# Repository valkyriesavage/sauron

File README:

Sauron
======
Sauron is a tool for prototyping functional objects, like video game
controllers, DJ mixers, or ergonomic mice. It works on computer vision, so
you don't have to spend time wiring up each button or joystick that you want
in your final prototype: a single camera can see them all.

The way it works is this: first, you create a 3D model of your object in
Solidworks, and put in special tagged geometry so Sauron knows what to look
for:

Then, you add in a 3D model which represents the camera you plan to use for
sensing. It's field of vision also needs to be modeled and tagged:

As you start working through the user interface, Sauron will do some analysis
on the locations of the parts in your object:

First, we decide if there's anything that already falls in the camera's
field of view (FOV). In this case, the joystick and D-Pad on the front
of the controller are already visible.

So we ignore those.

Sauron can also extrude pieces to go into the camera's field of view. The
bumper buttons on the side of the controller were processed in this way:

Originally they were stumpy little tagged geometry pieces,

But we just stretch them until they reach the FOV cone.

So, those are done once we extend them.

So we'll ignore them for now.

These buttons in the back are a different problem. We could extend them until
they hit the FOV cone, but unfortunately they'll hit the controller body if we
do that. Sauron does simulation to check, and finds that that's true.

So we'll have to go for plan B. Sauron's plan B is mirrors. We can figure out
where the mirrors need to go by doing raycasting: the camera sends out a bunch
of rays, looks at where they go after they bounce off the inside surface of the
controller, and checks to see if any of them actually hit the buttons we're
looking for. All the ones that do are shown here. Sauron will put stars to
indicate where a mirror should go after printing (the camera will be able
to see the reflection of the buttons in the mirror):

So, all put together, our processed controller looks like this:

And when we print it out, we attach the camera that we modeled, color the
buttons, add the mirrors, and show it to the computer vision algorithms.
Then we're set to go!

Sauron supports several kinds of inputs, which have different kinds of
motion, like buttons, dials, trackballs, and sliders.
![modeled object](images/sauron-inputs.png "Sauron takes a wide range
of inputs!") 
You can make your own inputs if you want to code up the computer vision
algorithms for them, but you can also just modify the existing inputs
to fit your needs, like turning a dial into a volume knob or a DJ
mixing wheel:

The computer vision works in different ways depending on the way the
component moves. You can dig around and check it out, but the gist
is this:

Technical Details
=================
The Sauron model-modification tool is written as a plugin for SolidWorks.
I wrote and tested it on SW2012, but theoretically it will work in newer
versions of that tool. The computer vision subsystems are written with
OpenFrameworks, and everything in here communicates via OSC messages.

Here there be Dragons
=====================
This code was written as a part of my PhD, and thus it can be sketchy in
some places! It's not very well documented, but I wanted to provide it
on github for anyone curious about spelunking through it and hopefully
making use of it in some way.

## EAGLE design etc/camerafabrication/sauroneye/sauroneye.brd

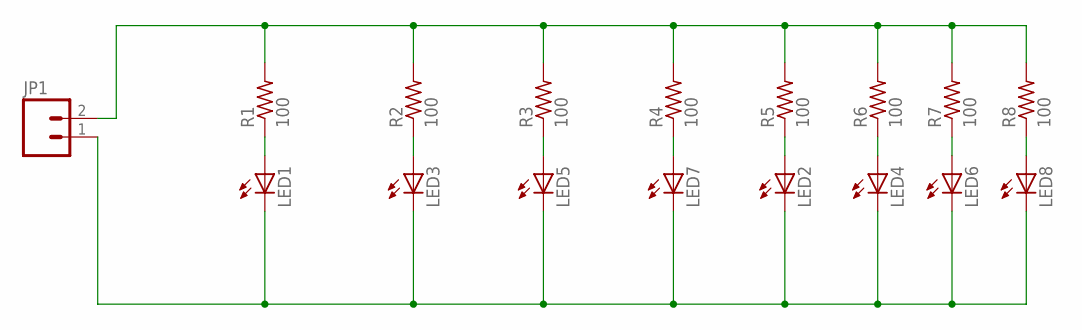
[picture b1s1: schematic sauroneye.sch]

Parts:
JP1: M02PTH; 1X02
LED1, LED2, LED3, LED4, LED5, LED6, LED7, LED8: LEDCHIP-LED0805; CHIP-LED0805
R1, R2, R3, R4, R5, R6, R7, R8: 100; R0805

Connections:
unnamed: JP1.2, R1.2, R2.2, R3.2, R4.2, R5.2, R6.2, R7.2, R8.2
unnamed: LED1.A, R1.1
unnamed: LED3.A, R2.1
unnamed: LED5.A, R3.1
unnamed: LED7.A, R4.1
unnamed: JP1.1, LED1.C, LED2.C, LED3.C, LED4.C, LED5.C, LED6.C, LED7.C, LED8.C
unnamed: LED2.A, R5.1
unnamed: LED4.A, R6.1
unnamed: LED6.A, R7.1
unnamed: LED8.A, R8.1

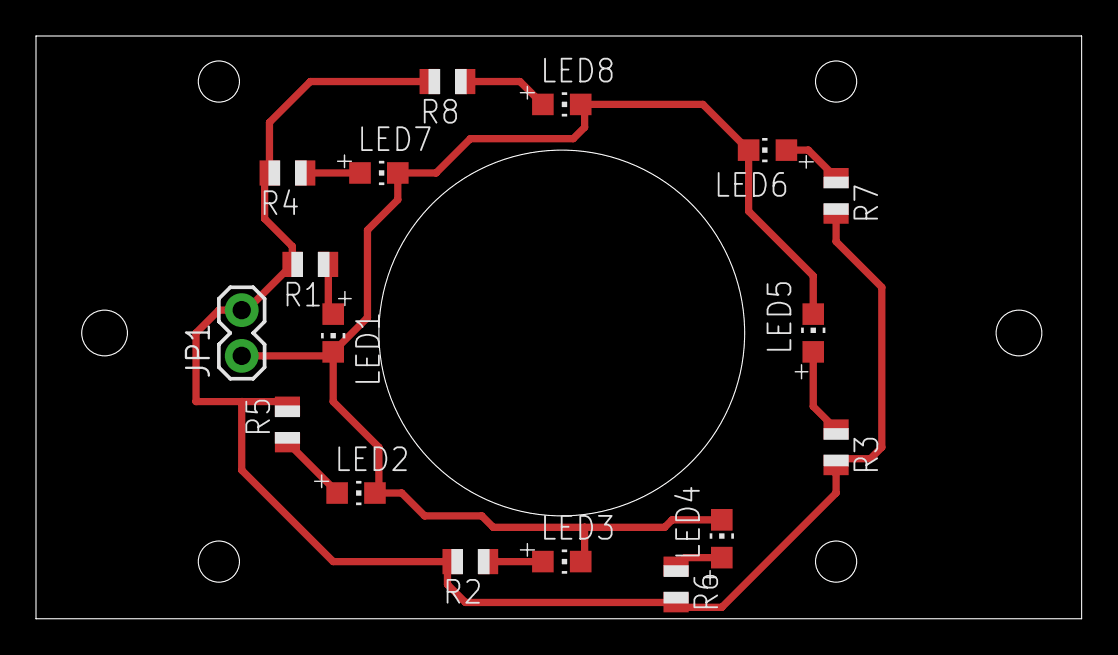
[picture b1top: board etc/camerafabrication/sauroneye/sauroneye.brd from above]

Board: 2 copper layers, 58.1 x 32.4 mm, 17 parts (0 on the bottom side), 10 nets.

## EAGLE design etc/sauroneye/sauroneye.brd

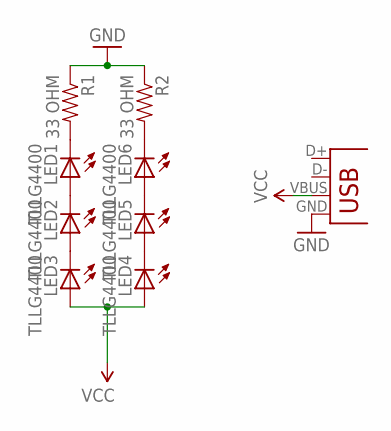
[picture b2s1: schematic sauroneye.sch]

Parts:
LED1, LED2, LED3, LED4, LED5, LED6: TLLG4400; LED3MM
R1, R2: 33 OHM; AXIAL-0.3
X1: USBSMD; USB-MINIB

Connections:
GND: R1.P$1 (1), R2.P$1 (1), X1.GND
unnamed: LED6.K (C), R2.P$2 (2)
unnamed: LED1.K (C), R1.P$2 (2)
unnamed: LED5.K (C), LED6.A
unnamed: LED4.K (C), LED5.A
unnamed: LED1.A, LED2.K (C)
unnamed: LED2.A, LED3.K (C)
VCC: LED3.A, LED4.A, X1.VBUS

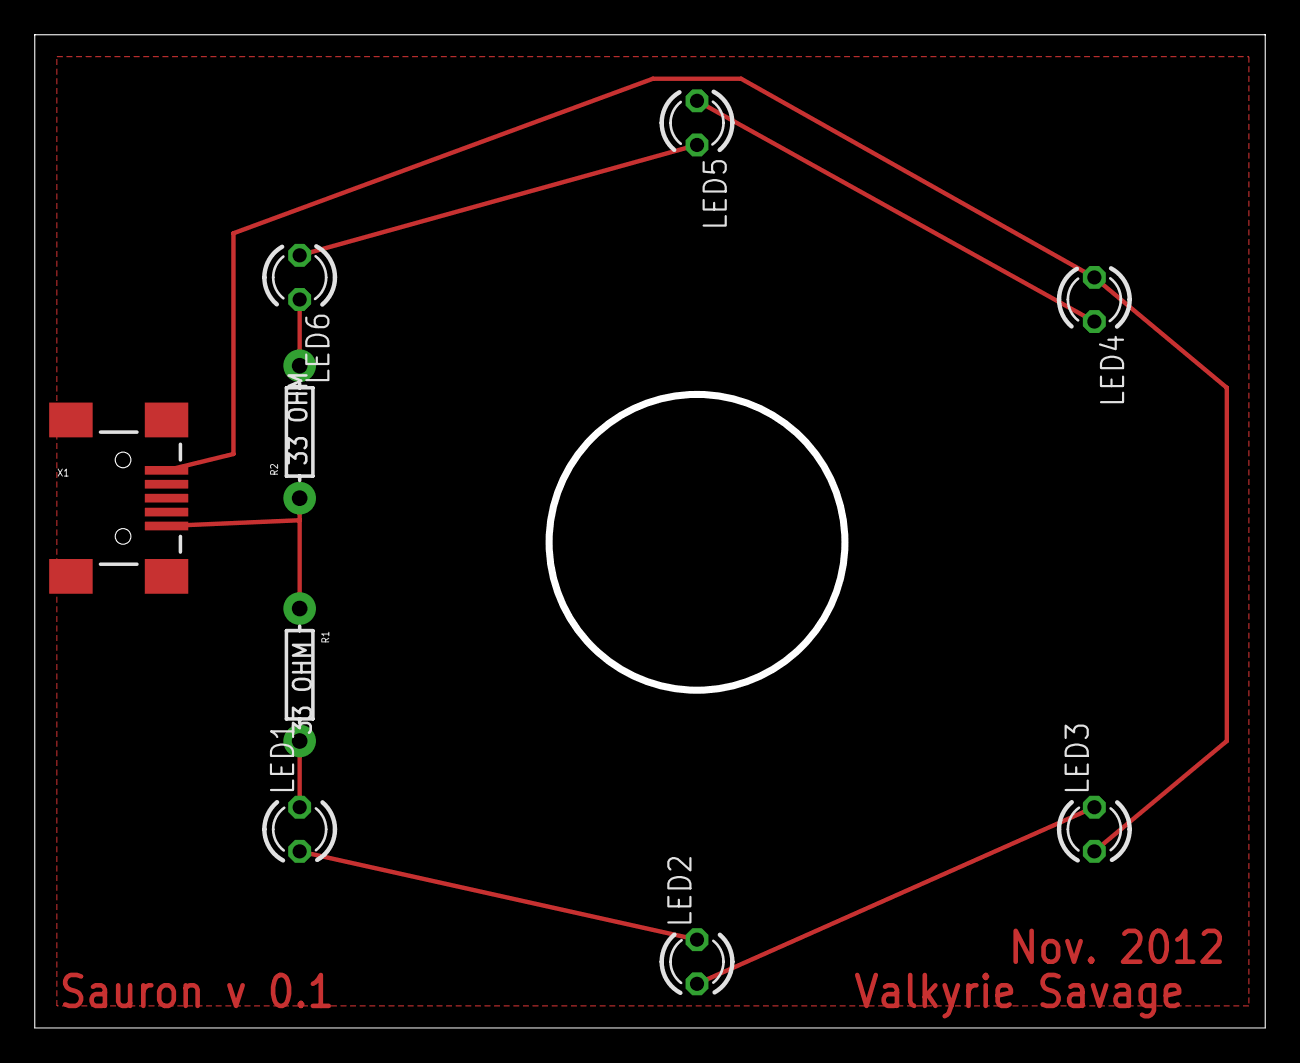
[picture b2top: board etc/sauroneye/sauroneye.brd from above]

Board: 2 copper layers, 70.4 x 56.7 mm, 9 parts (0 on the bottom side), 8 nets.

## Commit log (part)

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2012-07-09 Initial commit with skeleton README abstract
2012-07-11 small iterations on mockup
2012-08-09 adding gitignore
2012-08-10 BinaryRings update
    * ridges are now wider
    * colors for better visibility
    * measurement arm for wires, includes guides and a skirt to keep its
    place
2012-08-11 Switch.scad
    * it seems useful to have a switch description that we can just
    subtract out or add in to a model
2012-08-23 Switch ring and update to switch
    * switch ring like the one in the animal sounds toy
    * switch is now properly a module
2012-11-04 First version of vision algorithm, totally crippled
    * The vision algorithm is now something that I found online
    which displays interesting corners to track
    * Thanks to kristi.tsukida@gmail.com for putting it out there!
2012-11-05 Return a list of threshold-exceeding points
    * can do more calculation on them!
2012-11-09 circuit board for around eye camera
    * has a cutout for the eye to fit through
    * has 6 IR LEDs around to light the space
2012-11-12 update to board
    * board now obeys physics and laws of electricity
    * board has USB connector
    * removing whatever those spurious eagle files are and ignoring them
    in the future
2012-11-14 SolidWorks design for first interactive object
    * button - need to iterate on this; currently only vertical motion
    and we need horizontal
    * dial
    * slider
    * dpad - will need physical testing for springs
    * body - should hold point grey camera + extra IR LED board
2012-11-15 Calibration page for Point Grey Camera
    * a page with one inch squares on it so we can
    determine FOV and lens angle for the point grey
2012-11-20 modify for printing and camera measurements
    * now should be printable, the box1
    * now takes into account PS3 EYE FOV
    * started on slider+joystick box
    * slider and joystick both modeled
2012-11-21 joystick ready to print, i think
    * modified part to fit together!
    * joystick obeys physics!
    * yayyyyyyyy
    * let's print it
2012-11-26 paper skeleton
    * woooooooooo paper!
2012-11-30 skeleton for component trackers
    * need to implement all detection algorithms
    * need to figure out if contourfinder finds blobs in the same
    order each time
    * need to test!
2012-12-05 everything should compile now, fixed some compiler errors and re-indented header file
2012-12-12 change board opening to hold ps3 eye, change to work properly with smc usb connector
2012-12-12 sauroneye board bugfixing
2012-12-12 paper starting!
    * paper formatted correctly
    * sauron example image
    * now to write a bunch...
2012-12-13 more paper fleshing-out
2012-12-16 paper work
2012-12-16 related work
2012-12-19 photos of hardware setup
2012-12-27 added a testing thing which still needs work, working on redoing some of the coding for tracking
2013-01-09 bjoern's comments
2013-01-11 moved from CHI-WIP to UIST to reflect real life..
2013-01-14 moving to UIST folder from CHI folder
    * remove extraneous CHI class
    * having issues with TeX; it won't take all the files
    at once...
2013-01-14 start on controller-shaped thing
    * git ignore solidworks "file open" files
    * dpad post size changes
    * minor modifications to box
    * 4-post style button for even springiness
    * xbox-style body with button holes and dpad holes so far (need
    joystick)
2013-01-17 iteration
2013-01-22 moved some stuff, finished some models!
    * moved a few of the button assemblies into their own folders
    to avoid clutter
    * finished the multi-linkage button of Bjoern's design
    * finished adding the joystick to the XBOX-style controller
    * finished a preliminary design for a button with a whippy thing
    which could be better than the multi-linkage solution?
2013-01-27 resolved 'ISO forbids initialization of member' error. see: -http://www.cplusplus.com/forum/beginner/37023/ -http://stackoverflow.com/questions/177437/const-static
2013-02-01 finally figure out how to work with SW API in VS, about to upgrade to using VS2012 Professional, so this is a checkpoint
2013-02-02 registration: added more structure and some bulk
2013-02-04 outline of how to capture slider bounds
2013-02-05 experimenting with configurations, fixed FOV objects to be more accurate, playing around with features
2013-02-06 added a cin utility function
2013-02-08 modifications for ease of coding
2013-02-09 utilities: added bounding box utility function
2013-02-10 should now be able to read the percentage progress of a slider in a horizontal environemnt. Testing with a printed controller pending. Limited functionality to ensure I'm doing it correctly (so, pend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
2013-02-13 refactored slider stuff and started with dial detection/calculation
2013-02-17 more dial work -some utility methods (distanceFormula, midpoint) -redid dial registration methods to reflect actuality of how blobs will appear to camera -progress detection, feedback pending
2013-02-18 configurations now work
    * can create and activate configurations of parts instead of using the
    copy-a-part method.
    * yay!
2013-02-18 now generate configurations, can't get it to do extrusion correctly
    * still working on extrusion
    * about to start experiments with measurement... maybe we can
    just extrude that way for now.
2013-02-18 modifications to make coding easier
2013-02-21 frustratingly, extrusion depth change still does not work properly. we can change in default config only, and only when we are in another config. then we cannot automatically change back and have the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
2013-02-22 scroll wheel progress
    -todo: have it not show 'none' direction unconditionally
2013-02-23 cleaned up, refactored, and added message sending message will send to 'componenttype/id/componentmeasurement'
2013-02-24 cleaned up a bit
2013-02-25 prepared registration for receiving messages from SW. Pressing 'r' simulates receving a start message and starting registration, pressing 'd' simulates receiving a finish message and stopping registr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
2013-02-26 now movement sensitive recognition is available for slider, dial, button and scroll_wheel
2013-02-27 looking at measure vs closest distance and feature vs config
    * still having default issues
    * still can't get accurate distance measurements
2013-02-27 AUTOMATICALLY MODIFIED MODELS!
    * many of these changes were automatic! by the plugin!
    * other changes are related to reorganizing the folder so i don't
    go insane
2013-03-01 added a bit of graphical niceties -informing the user what component is being registered
2013-03-01 cleaned up component registration
2013-03-02 added joystick support. -coordinate output isn't that meaningful to the region of interest yet. But it does offer correlative information to the position of the joystick
2013-03-02 removed old unused code
2013-03-03 messed around with movement threshold (still haven't settled on a good one), also corrected window size.
2013-03-05 altered joystick measurement so now points are relative to joystick's region of interest
2013-03-06 interface mockups for bjoern class
2013-03-06 some modifications...
2013-03-07 function signature and component size
    * changed function signature from bool to correct void
    * upped minimum trackable component size to 15 from 5 in order to
    reduce noise
2013-03-07 nasty node-ness
    * not sure if all this stuff has to be in the working directory, but
    here it is!
    * this is the addition of the node.js modules required to repeat the
    osc messages from the CV code over to WebSockets
    * note that to run this, one needs to install node
2013-03-07 add an ack for mark
2013-03-08 cleaned up ComponenTracker construction. -mThreshold at 2.0f seems like a good guess
2013-03-08 Dial measurements now make sense according to a 360 degree circle of completion. Return is in degrees -ok you'll probably want to choose between degrees and radians so I added that in
2013-03-08 improved scroll wheel feedback. Still has some quirks like sometimes it fails to pick up direction
2013-03-08 trying to get raytracing to work... slightly works now in that it no longer crashes solidworks
2013-03-08 enforce ordering of button pushes, export STL file after removing camera, then replace camera
2013-03-10 0th order ray-tracing works!
    * thanks be to Artem Taturevych of Intercad for all his help in
    the SolidWorks forums. progress!
    * this simplified version of raytracing only casts one ray from
    the origin in the z direction and checks to see if it hits the
    selected solid body, then visualizes the points where it does
2013-03-10 make button have just one solid body
2013-03-10 images for the generated web instructions
2013-03-10 added camera holders to the two hand-tuned components (need to tweak for actual camera measurements), slid stuff around
2013-03-10 hand-tuned button with mirror setup to show how to place mirrors to alter button direction
2013-03-11 update camera model
    * real measurements!
    * change many models to reflect the actual size!
2013-03-12 remodeled things to have correct taps for camera mounting, dodecahedron, mirror thing, and linkage button are all ready to print
2013-03-12 fresh solidworks mockup with just one interface
2013-03-12 small paper tweak
2013-03-13 still raytracing...
2013-03-13 try out the joystick as a dpad, thicken the dpad thingies
2013-03-15 changes mostly to related work
2013-03-18 extrusion now works really really well
    * updated measurement between a part and the FOV to cast a ray in the
    direction of the flag protrusion... this gives the best reading and
    can also reliably tell when we won't be able to reach the FOV
    * updated all components to have the correct features to make this ray
    casting work properly
2013-03-18 some figures
2013-03-18 some bits about assembly mate moving (does not work) and some bits about checking to see if other components block rays
2013-03-20 added example images into instructions
    * generated instructions now show images
    * yay!
2013-03-20 put joystick part to replace assembly in controller
2013-03-21 tweaked some figures, added comments
2013-03-23 joystick readjusted so middle is (0,0) and fixed a joystick bug (the bug was trying to make calculations across every blob in the view (including those outside it's ROI) which obviously won't work).
2013-03-25 paper work, new figures
2013-03-25 ergonomic mouse first cut
2013-03-25 abstractions are nice
2013-03-25 added some ComponentTracker documentation
2013-03-26 updated and new figures, language, bits of evaluation, hooray
2013-03-26 edge cases
2013-03-26 added some documentation
2013-03-27 added some arduino test code (untested)
2013-03-27 multinub button for figure now working
2013-03-27 sad and broken
2013-03-28 just add in the else to keep away from that weird case where they are both set
2013-03-28 remove TODO
2013-03-28 extrusion failure figure
2013-03-29 quick check will highlight which components are visible or not to the camera
2013-03-29 new figures from xbox processing and more, with one figure ugly and incomplete (the arch one)
2013-03-30 add a flag for black vs white prints, revert dial to previous sensing
2013-03-31 Bjoern's pass over related work
2013-04-02 extra sentence in limitations
2013-04-02 updated figures, some work on wording
2013-04-02 updated dpad algorithm to something more reasonable
2013-04-02 figures and video clips
2013-04-02 figures that i thought went away
2013-04-02 last of sw images, i do believe
2013-04-04 pass over pages 1-3
2013-04-04 game now accepts osc messages, should process them correctly
2013-04-04 this demo code now works
2013-04-04 i thought this was already gone?
2013-04-04 comment resolution
2013-04-05 typos and a new figureeeee
2013-04-05 fixed figure to have reference letters
2013-04-05 notes about camera difficulties added to evaluation section in dj mixer
2013-04-05 finished pass through the end; comments left to address; added better pipe cam figure and trackball photos
2013-04-05 update scroll wheel code for better demo
2013-04-08 final submitted draft
2013-04-16 small doc about creating new components
2013-05-10 camera extrusion debuggerated, new sexiness for many functions
2013-05-17 real reference for stefanie
2013-05-18 first pass over all reviewer comments
2013-05-21 untested thresholding code for finding x direction
2013-06-09 beginning to do rewrite
2013-06-13 towards final draft quote unquote
2013-07-27 bjoern's editing passa
2016-03-17 UIST stuff
2016-03-17 remove old stuff not necessary for public release, pretty README

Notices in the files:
parts and their libraries:
SparkFun-Connectors: Licensing: CC v3.0 Share-Alike You are welcome to use this library for commercial purposes.
